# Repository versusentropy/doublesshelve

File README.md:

# doublesshelve

## WORK-IN-PROGRESSS - NOT TESTED YET

my stereo version of shelves done in KiCad.

CC-BY-SA 3.0 

Original by Emilie Gillet. Thank you for everything.
https://github.com/pichenettes/eurorack

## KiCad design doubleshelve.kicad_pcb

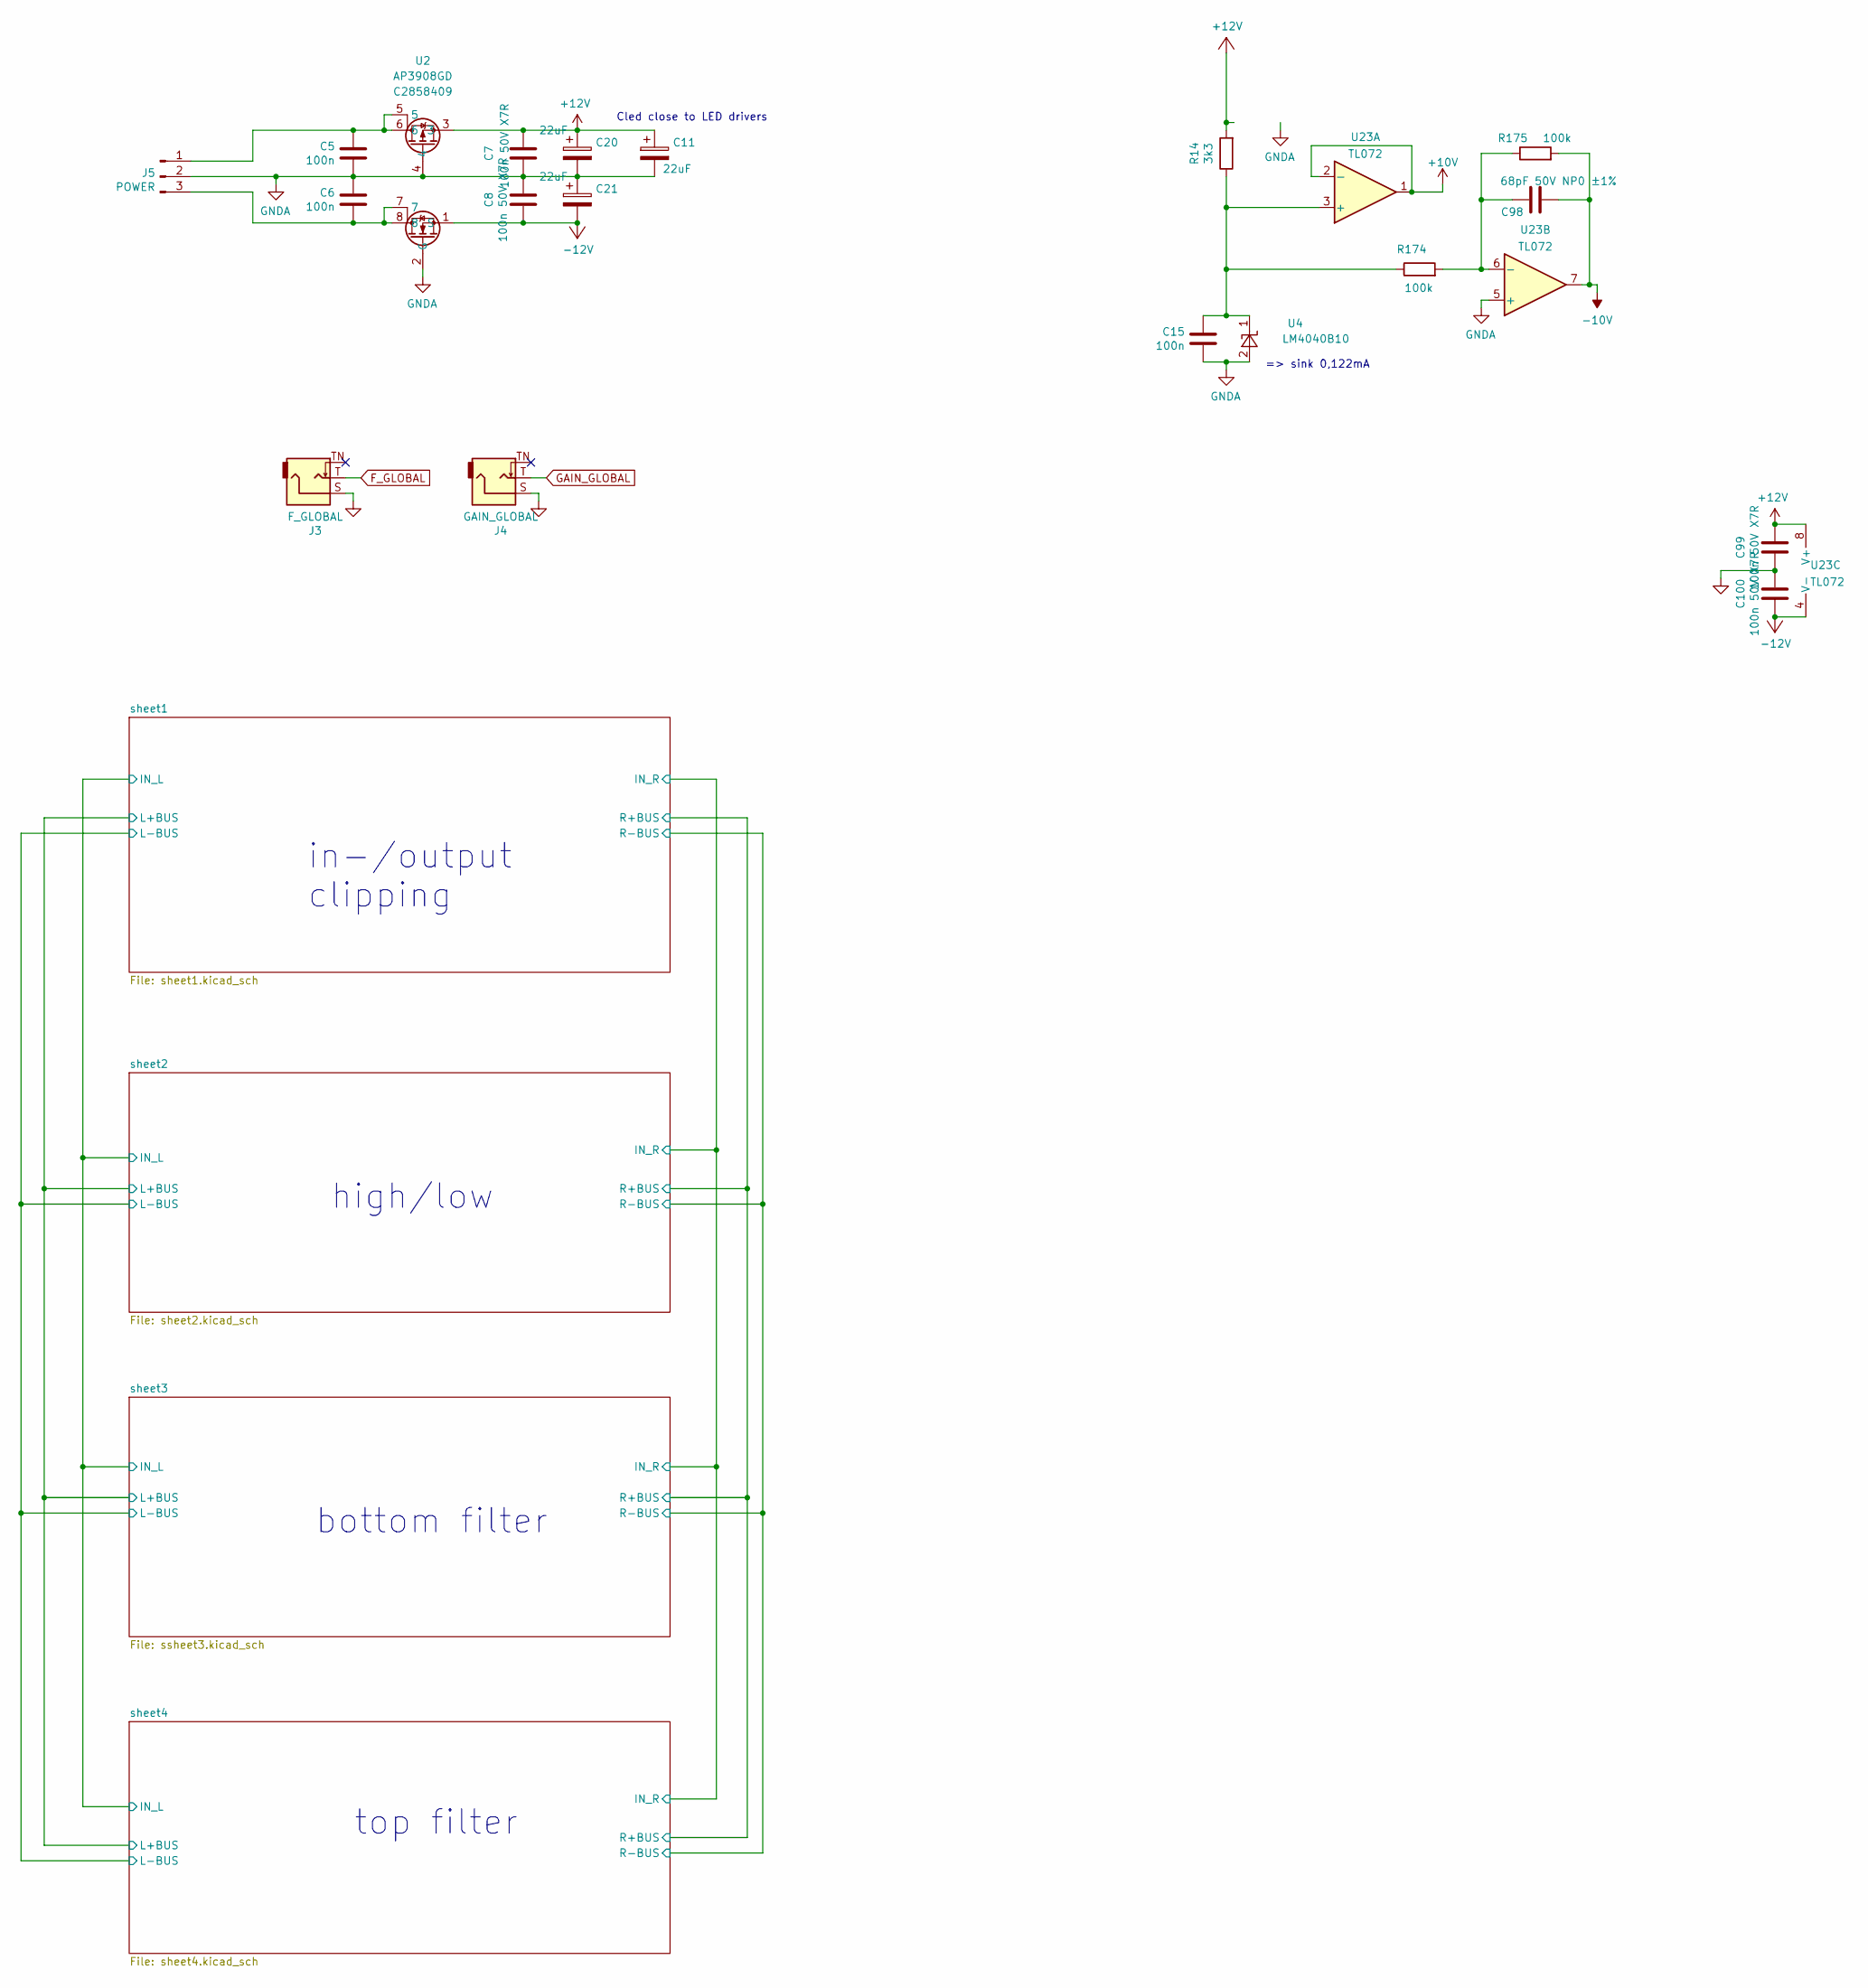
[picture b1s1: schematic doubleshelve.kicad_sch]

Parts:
C5, C6, C15: 100n; C_0402_1005Metric
C7, C8, C99, C100: 100n 50V X7R; C_0402_1005Metric; LCSC C307331
C11, C20, C21: 22uF; CP_Elec_5x5.3; LCSC C2163349
C98: 68pF 50V NP0 ±1%; C_0402_1005Metric; LCSC C5182453
J3: F_GLOBAL; Jack_3.5mm_QingPu_WQP-PJ398SM_Vertical_CircularHolesSMALL
J4: GAIN_GLOBAL; Jack_3.5mm_QingPu_WQP-PJ398SM_Vertical_CircularHolesSMALL
J5: POWER; eurorac_power-v2
R14: 3k3; R_0402_1005Metric
R174, R175: 100k; R_0402_1005Metric; LCSC C319963
U2: AP3908GD; LCSC C2858409
U4: LM4040B10; SOT-23
U23: TL072; SOIC-8_3.9x4.9mm_P1.27mm

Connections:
+10V: U23.1, U23.2 (-); also elsewhere on the board
+12V: C7.2, C11.1, C20.1, C99.2, R14.2, U2.3, U23.8 (V+); also elsewhere on the board
-10V: C98.1, R175.2, U23.7; also elsewhere on the board
-12V: C8.1, C21.2, C100.1, U2.1 (S), U23.4 (V-); also elsewhere on the board
F_GLOBAL: J3.T; also elsewhere on the board
GAIN_GLOBAL: J4.T; also elsewhere on the board
GNDA: C5.1, C6.2, C7.1, C8.2, C11.2, C15.1, C20.2, C21.1, C99.1, C100.2, J3.S, J4.S, J5.2, U2.2 (G), U2.4, U4.2 (A), U23.5 (+); also elsewhere on the board
unnamed: C5.2, J5.1, U2.5, U2.6
unnamed: C6.1, J5.3, U2.7, U2.8
unnamed: C15.2, R14.1, R174.1, U4.1 (K), U23.3 (+)
unnamed: C98.2, R174.2, R175.1, U23.6 (-)

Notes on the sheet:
Cled close to LED drivers
in-/output clipping
high/low
top filter
bottom filter
=> sink 0,122mA

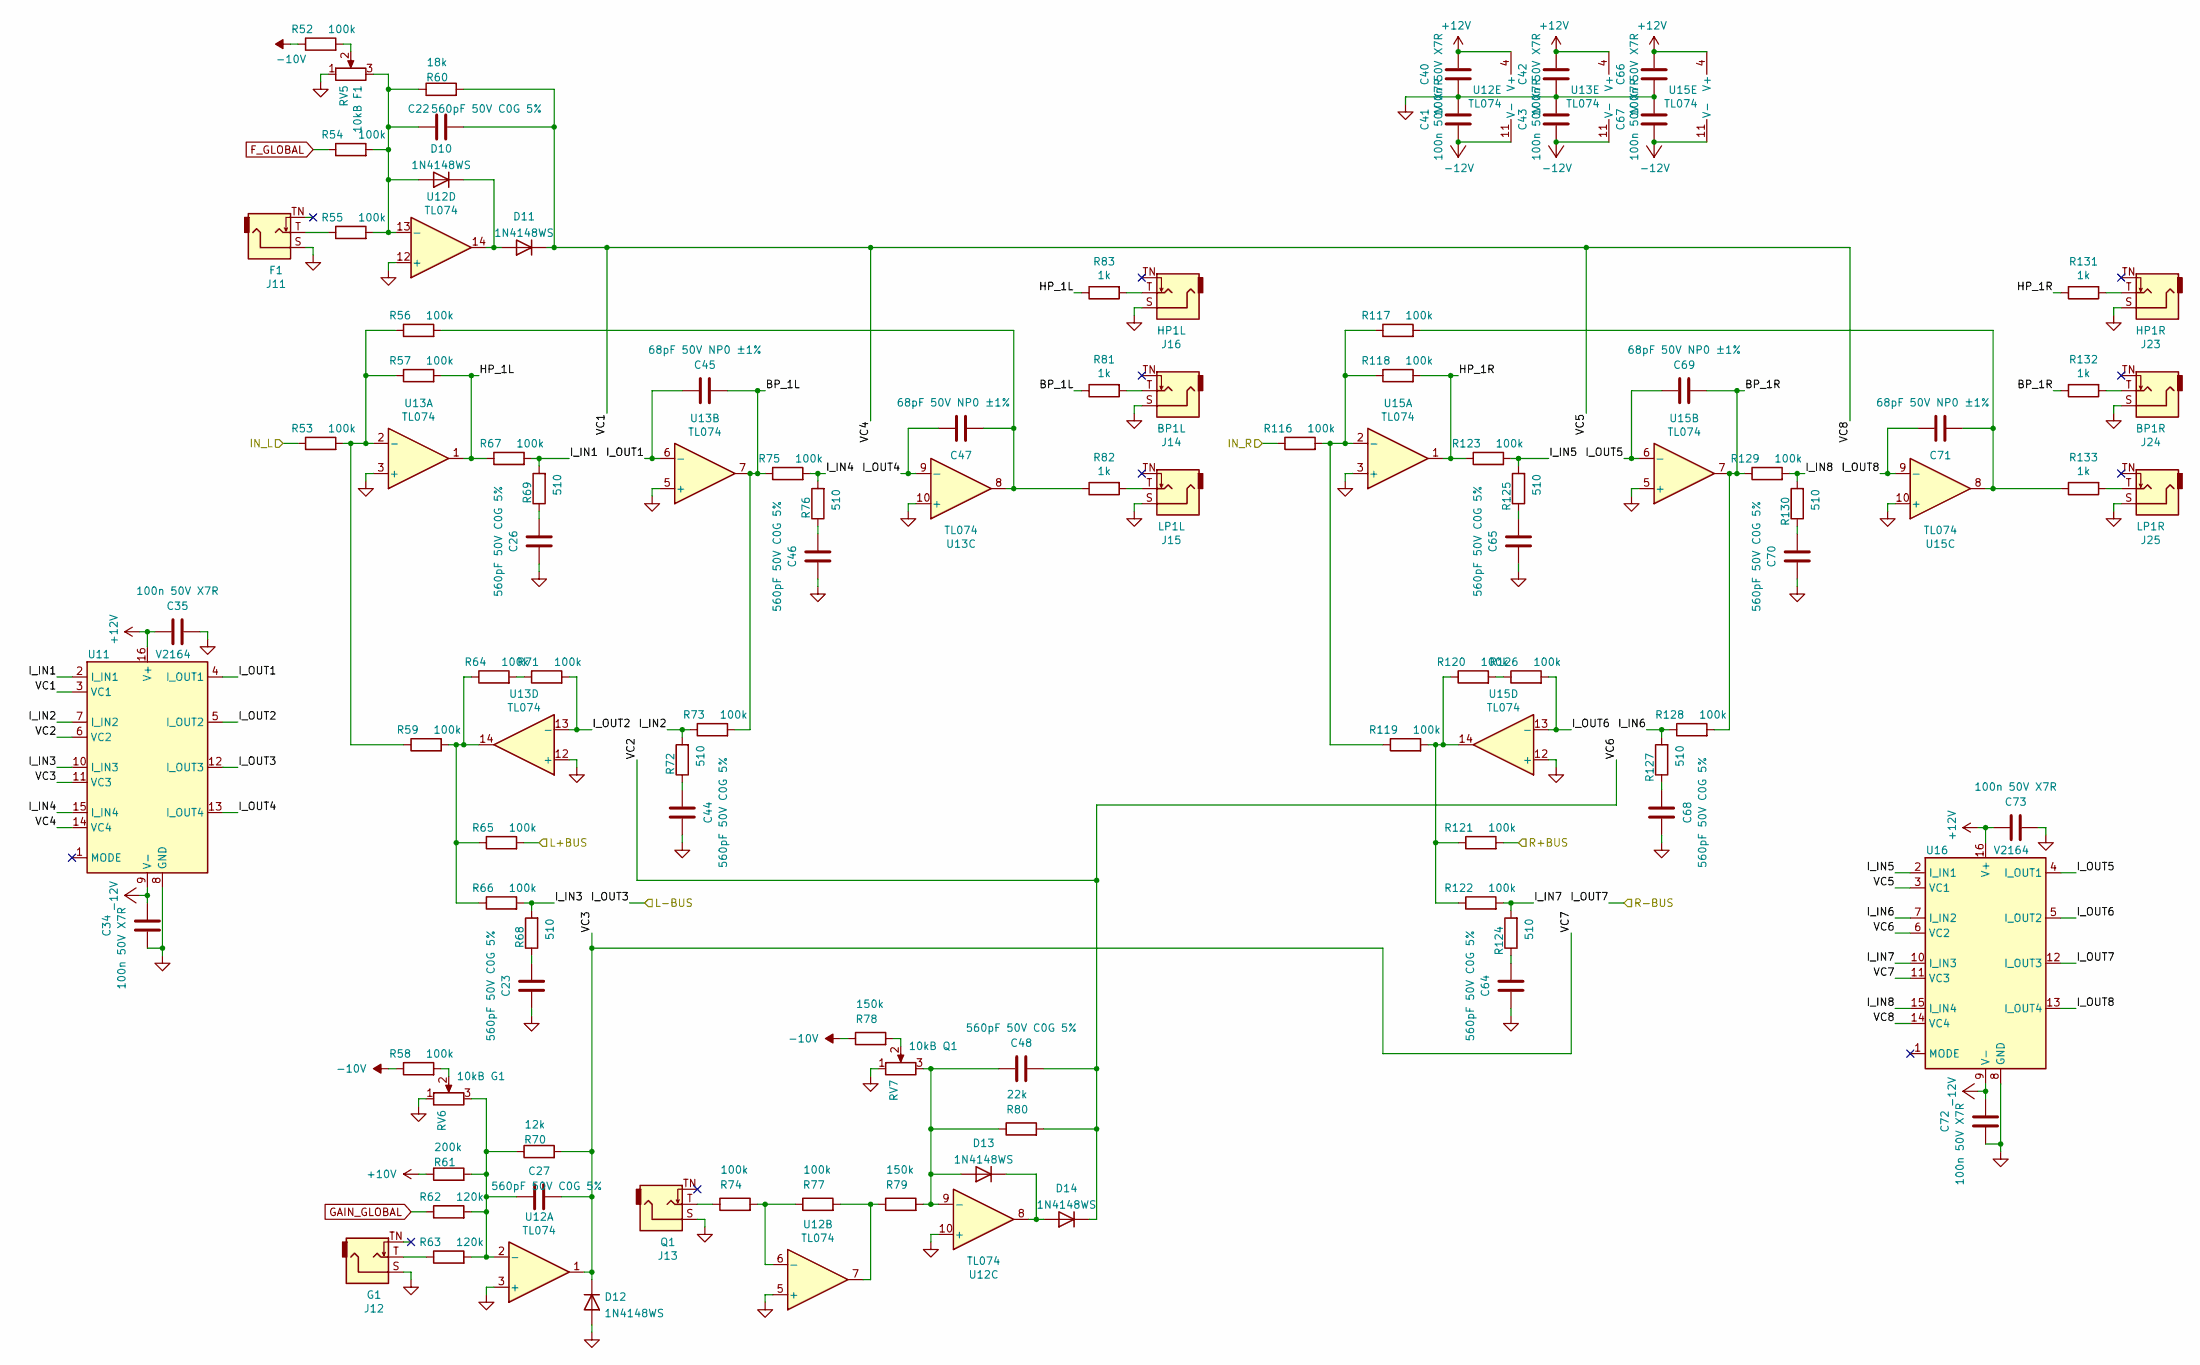
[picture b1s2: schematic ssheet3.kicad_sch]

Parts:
C22, C23, C26, C27, C44, C46, C48, C64, C65, C68, C70: 560pF 50V C0G 5%; C_0603_1608Metric; LCSC C97881
C34, C35, C40, C41, C42, C43, C66, C67, C72, C73: 100n 50V X7R; C_0402_1005Metric; LCSC C307331
C45, C47, C69, C71: 68pF 50V NP0 ±1%; C_0402_1005Metric; LCSC C5182453
D10, D11, D12, D13, D14: 1N4148WS; D_SOD-323; LCSC C2128
J11: F1; Jack_3.5mm_QingPu_WQP-PJ398SM_Vertical_CircularHolesSMALL
J12: G1; Jack_3.5mm_QingPu_WQP-PJ398SM_Vertical_CircularHolesSMALL
J13: Q1; Jack_3.5mm_QingPu_WQP-PJ398SM_Vertical_CircularHolesSMALL
J14: BP1L; Jack_3.5mm_QingPu_WQP-PJ398SM_Vertical_CircularHolesSMALL
J15: LP1L; Jack_3.5mm_QingPu_WQP-PJ398SM_Vertical_CircularHolesSMALL
J16: HP1L; Jack_3.5mm_QingPu_WQP-PJ398SM_Vertical_CircularHolesSMALL
J23: HP1R; Jack_3.5mm_QingPu_WQP-PJ398SM_Vertical_CircularHolesSMALL
J24: BP1R; Jack_3.5mm_QingPu_WQP-PJ398SM_Vertical_CircularHolesSMALL
J25: LP1R; Jack_3.5mm_QingPu_WQP-PJ398SM_Vertical_CircularHolesSMALL
R52, R53, R54, R55, R56, R57, R58, R59, R64, R65, R66, R67, R71, R73, R74, R75, R77, R116, R117, R118, R119, R120, R121, R122, R123, R126, R128, R129: 100k; R_0402_1005Metric; LCSC C319963
R60: 18k; R_0402_1005Metric
R61: 200k; R_0402_1005Metric
R62, R63: 120k; R_0402_1005Metric
R68, R69, R72, R76, R124, R125, R127, R130: 510; R_0402_1005Metric
R70: 12k; R_0402_1005Metric
R78, R79: 150k; R_0402_1005Metric
R80: 22k; R_0402_1005Metric
R81, R82, R83, R131, R132, R133: 1k; R_0603_1608Metric; LCSC C394536
RV5: 10kB F1; RD901F-ALPHA-POT
RV6: 10kB G1; RD901F-ALPHA-POT
RV7: 10kB Q1; RD901F-ALPHA-POT
U11, U16: V2164; SOIC-16_3.9x9.9mm_P1.27mm
U12, U13, U15: TL074; SOIC-14_3.9x8.7mm_P1.27mm; LCSC C96507

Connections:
+10V: R61.1; also elsewhere on the board
+12V: C35.2, C40.2, C42.2, C66.2, C73.2, U11.16 (V+), U12.4 (V+), U13.4 (V+), U15.4 (V+), U16.16 (V+); also elsewhere on the board
-10V: R52.1, R58.1, R78.1; also elsewhere on the board
-12V: C34.2, C41.1, C43.1, C67.1, C72.2, U11.9 (V-), U12.11 (V-), U13.11 (V-), U15.11 (V-), U16.9 (V-); also elsewhere on the board
/sheet1/IN_L: R53.1; also elsewhere on the board
/sheet1/IN_R: R116.1; also elsewhere on the board
/sheet1/L+BUS: R65.2; also elsewhere on the board
/sheet1/R+BUS: R121.2; also elsewhere on the board
/sheet3/BP_1L: C45.1, R73.2, R75.1, R81.1, U13.7
/sheet3/BP_1R: C69.1, R128.2, R129.1, R132.1, U15.7
/sheet3/HP_1L: R57.2, R67.1, R83.1, U13.1
/sheet3/HP_1R: R118.2, R123.1, R131.1, U15.1
/sheet3/I_IN1: R67.2, R69.2, U11.2 (I_IN1)
/sheet3/I_IN2: R72.2, R73.1, U11.7 (I_IN2)
/sheet3/I_IN3: R66.2, R68.2, U11.10 (I_IN3)
/sheet3/I_IN4: R75.2, R76.2, U11.15 (I_IN4)
/sheet3/I_IN5: R123.2, R125.2, U16.2 (I_IN1)
/sheet3/I_IN6: R127.2, R128.1, U16.7 (I_IN2)
/sheet3/I_IN7: R122.2, R124.2, U16.10 (I_IN3)
/sheet3/I_IN8: R129.2, R130.2, U16.15 (I_IN4)
/sheet3/I_OUT1: C45.2, U11.4 (I_OUT1), U13.6 (-)
/sheet3/I_OUT2: R71.2, U11.5 (I_OUT2), U13.13 (-)
/sheet3/I_OUT3: U11.12 (I_OUT3); also elsewhere on the board
/sheet3/I_OUT4: C47.2, U11.13 (I_OUT4), U13.9 (-)
/sheet3/I_OUT5: C69.2, U15.6 (-), U16.4 (I_OUT1)
/sheet3/I_OUT6: R126.2, U15.13 (-), U16.5 (I_OUT2)
/sheet3/I_OUT7: U16.12 (I_OUT3); also elsewhere on the board
/sheet3/I_OUT8: C71.2, U15.9 (-), U16.13 (I_OUT4)
/sheet3/VC1: C22.1, D11.1 (K), R60.2, U11.3 (VC1), U11.14 (VC4), U16.3 (VC1), U16.14 (VC4)
/sheet3/VC2: C48.1, D14.1 (K), R80.2, U11.6 (VC2), U16.6 (VC2)
/sheet3/VC3: C27.1, D12.1 (K), R70.2, U11.11 (VC3), U12.1, U16.11 (VC3)
F_GLOBAL: R54.1; also elsewhere on the board
GAIN_GLOBAL: R62.1; also elsewhere on the board
GNDA: C23.2, C26.2, C34.1, C35.1, C40.1, C41.2, C42.1, C43.2, C44.2, C46.2, C64.2, C65.2, C66.1, C67.2, C68.2, C70.2, C72.1, C73.1, D12.2 (A), J11.S, J12.S, J13.S, J14.S, J15.S, J16.S, J23.S, J24.S, J25.S, RV5.1, RV6.1, RV7.1, U11.8 (GND), U12.3 (+), U12.5 (+), U12.10 (+), U12.12 (+), U13.3 (+), U13.5 (+), U13.10 (+), U13.12 (+), U15.3 (+), U15.5 (+), U15.10 (+), U15.12 (+), U16.8 (GND); also elsewhere on the board
unnamed: C23.1, R68.1
unnamed: C26.1, R69.1
unnamed: C44.1, R72.1
unnamed: C46.1, R76.1
unnamed: C47.1, R56.2, R82.1, U13.8
unnamed: C64.1, R124.1
unnamed: C65.1, R125.1
unnamed: C68.1, R127.1
unnamed: C70.1, R130.1
unnamed: C71.1, R117.2, R133.1, U15.8
unnamed: C22.2, D10.2 (A), R54.2, R55.2, R60.1, RV5.3, U12.13 (-)
unnamed: D10.1 (K), D11.2 (A), U12.14
unnamed: C48.2, D13.2 (A), R79.2, R80.1, RV7.3, U12.9 (-)
unnamed: D13.1 (K), D14.2 (A), U12.8
unnamed: J11.T, R55.1
unnamed: J12.T, R63.1
unnamed: J13.T, R74.1
unnamed: J14.T, R81.2
unnamed: J15.T, R82.2
unnamed: J16.T, R83.2
unnamed: J23.T, R131.2
unnamed: J24.T, R132.2
unnamed: J25.T, R133.2
unnamed: R52.2, RV5.2
unnamed: R58.2, RV6.2
unnamed: R59.2, R64.1, R65.1, R66.1, U13.14
unnamed: R64.2, R71.1
unnamed: R77.2, R79.1, U12.7
unnamed: R78.2, RV7.2
unnamed: R119.2, R120.1, R121.1, R122.1, U15.14
unnamed: R120.2, R126.1
unnamed: C27.2, R61.2, R62.2, R63.2, R70.1, RV6.3, U12.2 (-)
unnamed: R74.2, R77.1, U12.6 (-)
unnamed: R53.2, R56.1, R57.1, R59.1, U13.2 (-)
unnamed: R116.2, R117.1, R118.1, R119.1, U15.2 (-)

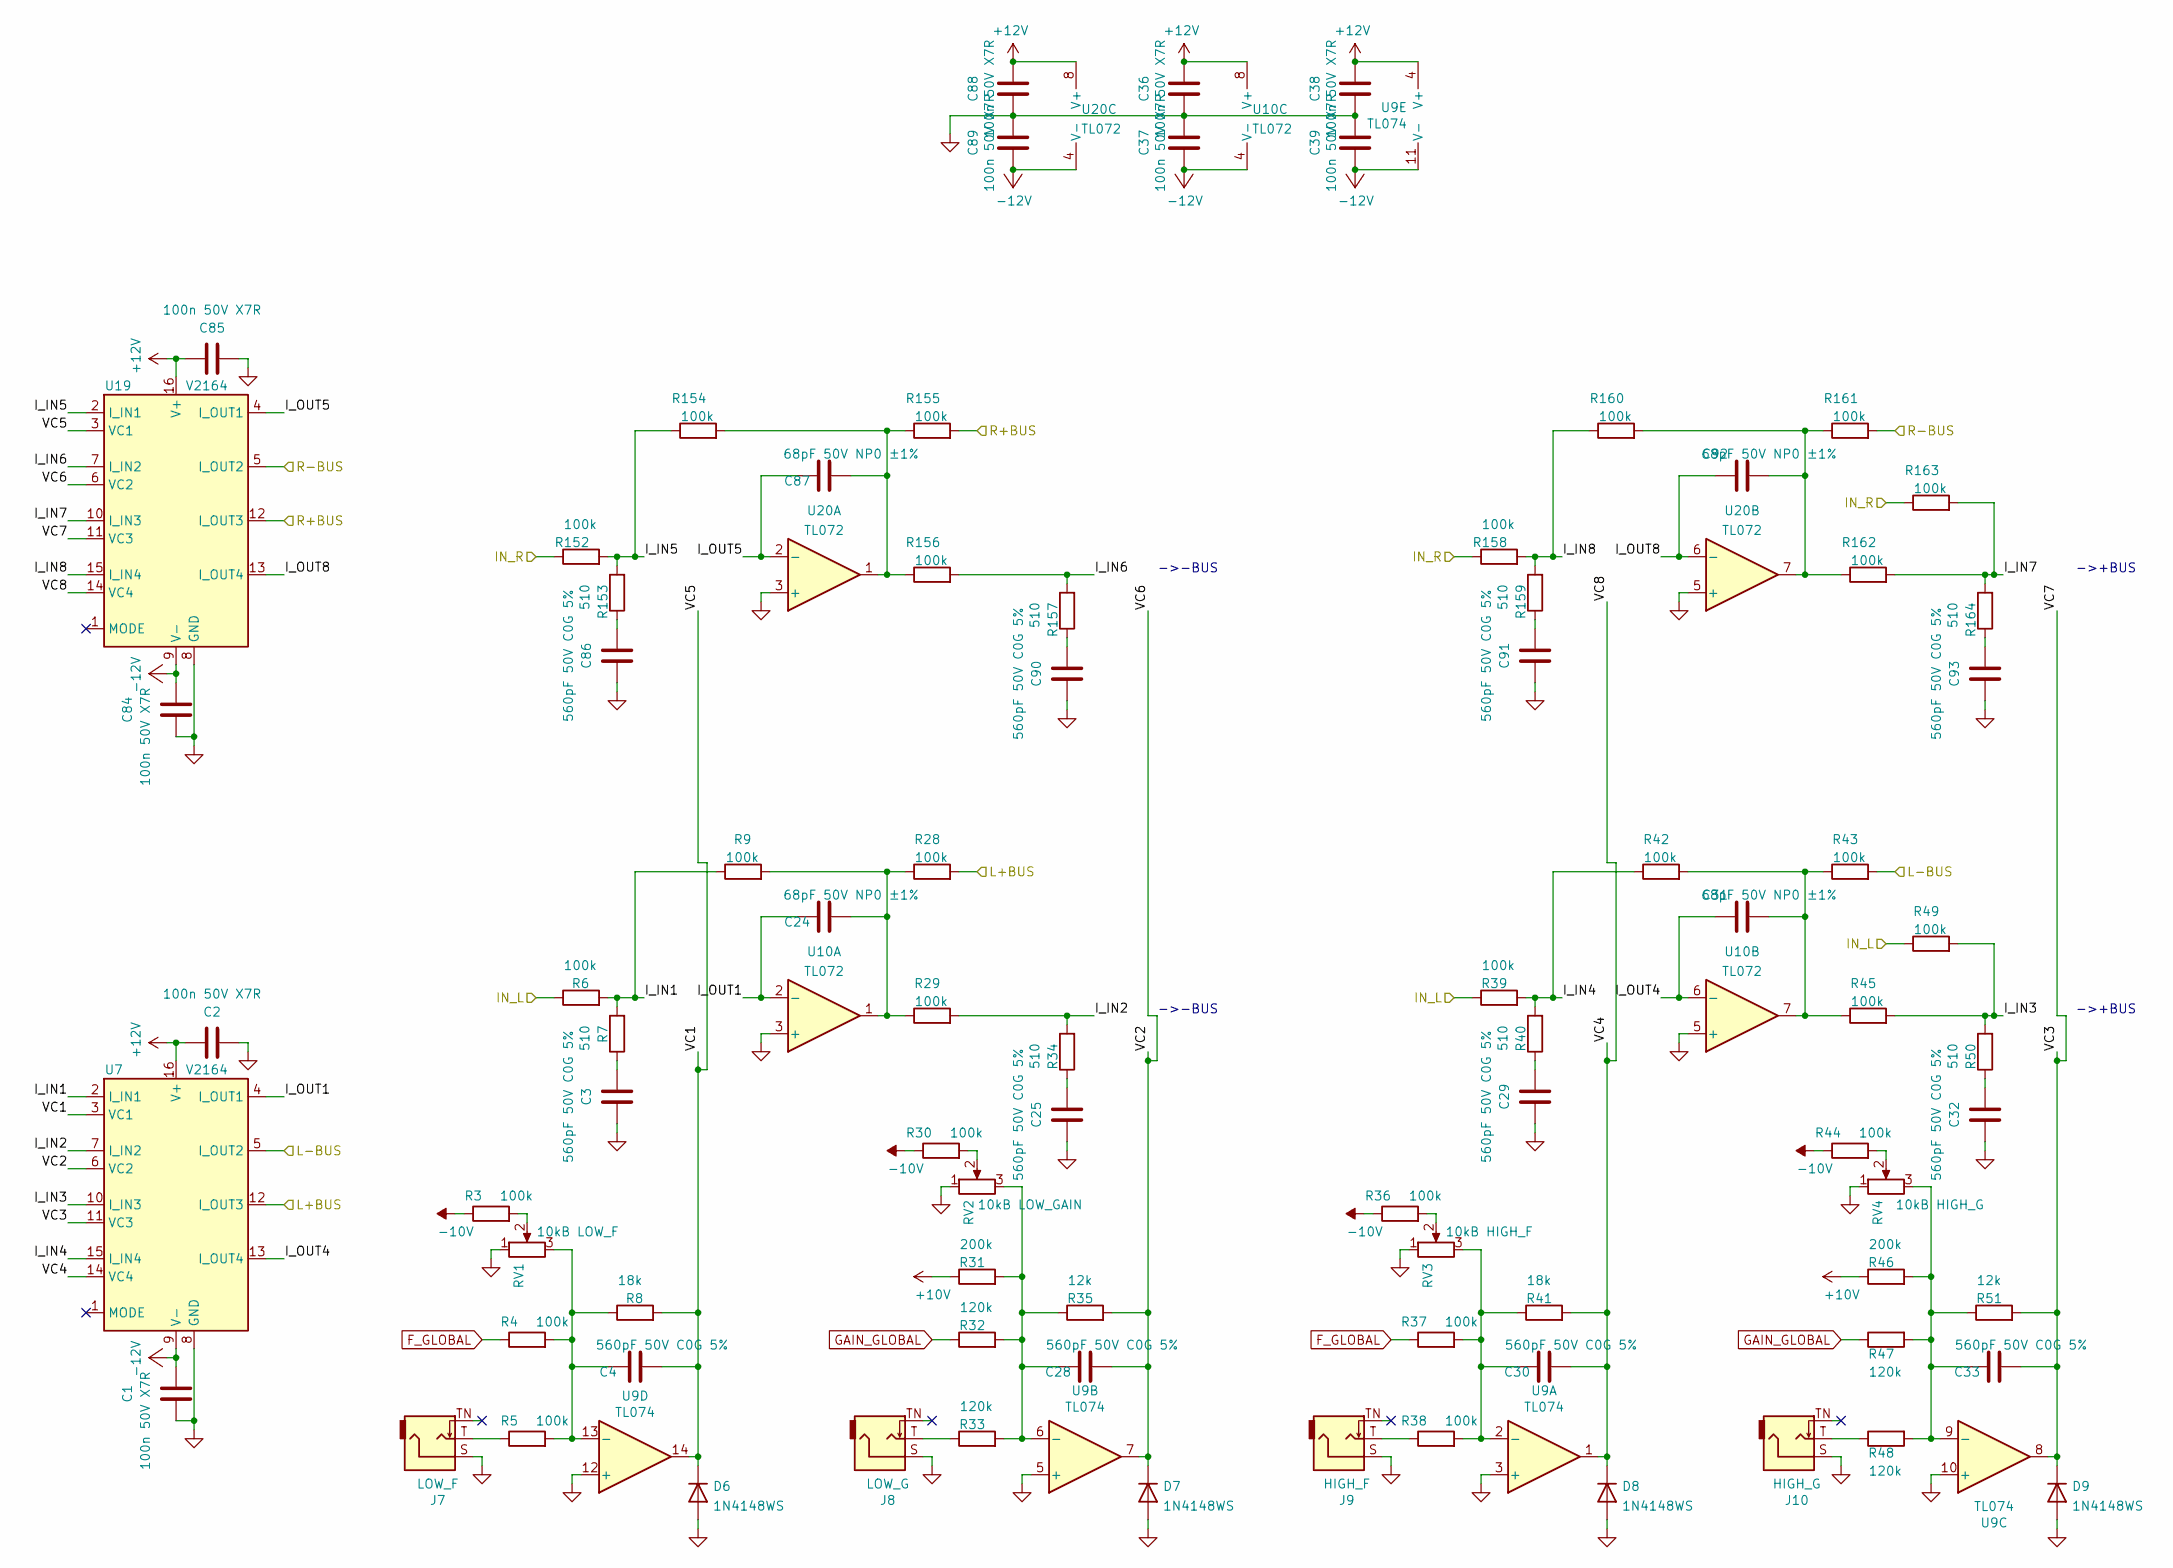
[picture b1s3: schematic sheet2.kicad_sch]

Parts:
C1, C2, C36, C37, C38, C39, C84, C85, C88, C89: 100n 50V X7R; C_0402_1005Metric; LCSC C307331
C3, C4, C25, C28, C29, C30, C32, C33, C86, C90, C91, C93: 560pF 50V C0G 5%; C_0603_1608Metric; LCSC C97881
C24, C31, C87, C92: 68pF 50V NP0 ±1%; C_0402_1005Metric; LCSC C5182453
D6, D7, D8, D9: 1N4148WS; D_SOD-323; LCSC C2128
J7: LOW_F; Jack_3.5mm_QingPu_WQP-PJ398SM_Vertical_CircularHolesSMALL
J8: LOW_G; Jack_3.5mm_QingPu_WQP-PJ398SM_Vertical_CircularHolesSMALL
J9: HIGH_F; Jack_3.5mm_QingPu_WQP-PJ398SM_Vertical_CircularHolesSMALL
J10: HIGH_G; Jack_3.5mm_QingPu_WQP-PJ398SM_Vertical_CircularHolesSMALL
R3, R4, R5, R6, R9, R28, R29, R30, R36, R37, R38, R39, R42, R43, R44, R45, R49, R152, R154, R155, R156, R158, R160, R161, R162, R163: 100k; R_0402_1005Metric; LCSC C319963
R7, R34, R40, R50, R153, R157, R159, R164: 510; R_0402_1005Metric
R8, R41: 18k; R_0402_1005Metric
R31, R46: 200k; R_0402_1005Metric
R32, R33, R47, R48: 120k; R_0402_1005Metric
R35, R51: 12k; R_0402_1005Metric
RV1: 10kB LOW_F; RD901F-ALPHA-POT
RV2: 10kB LOW_GAIN; RD901F-ALPHA-POT
RV3: 10kB HIGH_F; RD901F-ALPHA-POT
RV4: 10kB HIGH_G; RD901F-ALPHA-POT
U7, U19: V2164; SOIC-16_3.9x9.9mm_P1.27mm
U9: TL074; SOIC-14_3.9x8.7mm_P1.27mm; LCSC C96507
U10, U20: TL072; SOIC-8_3.9x4.9mm_P1.27mm

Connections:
+10V: R31.1, R46.1; also elsewhere on the board
+12V: C2.2, C36.2, C38.2, C85.2, C88.2, U7.16 (V+), U9.4 (V+), U10.8 (V+), U19.16 (V+), U20.8 (V+); also elsewhere on the board
-10V: R3.1, R30.1, R36.1, R44.1; also elsewhere on the board
-12V: C1.2, C37.1, C39.1, C84.2, C89.1, U7.9 (V-), U9.11 (V-), U10.4 (V-), U19.9 (V-), U20.4 (V-); also elsewhere on the board
/sheet1/IN_L: R6.1, R39.1, R49.1; also elsewhere on the board
/sheet1/IN_R: R152.1, R158.1, R163.1; also elsewhere on the board
/sheet1/L+BUS: R28.2, U7.12 (I_OUT3); also elsewhere on the board
/sheet1/R+BUS: R155.2, U19.12 (I_OUT3); also elsewhere on the board
/sheet2/I_IN1: R6.2, R7.2, R9.1, U7.2 (I_IN1)
/sheet2/I_IN2: R29.2, R34.2, U7.7 (I_IN2)
/sheet2/I_IN3: R45.2, R49.2, R50.2, U7.10 (I_IN3)
/sheet2/I_IN4: R39.2, R40.2, R42.1, U7.15 (I_IN4)
/sheet2/I_IN5: R152.2, R153.2, R154.1, U19.2 (I_IN1)
/sheet2/I_IN6: R156.2, R157.2, U19.7 (I_IN2)
/sheet2/I_IN7: R162.2, R163.2, R164.2, U19.10 (I_IN3)
/sheet2/I_IN8: R158.2, R159.2, R160.1, U19.15 (I_IN4)
/sheet2/I_OUT1: C24.2, U7.4 (I_OUT1), U10.2 (-)
/sheet2/I_OUT4: C31.2, U7.13 (I_OUT4), U10.6 (-)
/sheet2/I_OUT5: C87.2, U19.4 (I_OUT1), U20.2 (-)
/sheet2/I_OUT8: C92.2, U19.13 (I_OUT4), U20.6 (-)
/sheet2/VC1: C4.1, D6.1 (K), R8.2, U7.3 (VC1), U9.14, U19.3 (VC1)
/sheet2/VC2: C28.1, D7.1 (K), R35.2, U7.6 (VC2), U9.7, U19.6 (VC2)
/sheet2/VC3: C33.1, D9.1 (K), R51.2, U7.11 (VC3), U9.8, U19.11 (VC3)
/sheet2/VC4: C30.1, D8.1 (K), R41.2, U7.14 (VC4), U9.1, U19.14 (VC4)
/sheet3/I_OUT3: R43.2, U7.5 (I_OUT2); also elsewhere on the board
/sheet3/I_OUT7: R161.2, U19.5 (I_OUT2); also elsewhere on the board
F_GLOBAL: R4.1, R37.1; also elsewhere on the board
GAIN_GLOBAL: R32.1, R47.1; also elsewhere on the board
GNDA: C1.1, C2.1, C3.2, C25.2, C29.2, C32.2, C36.1, C37.2, C38.1, C39.2, C84.1, C85.1, C86.2, C88.1, C89.2, C90.2, C91.2, C93.2, D6.2 (A), D7.2 (A), D8.2 (A), D9.2 (A), J7.S, J8.S, J9.S, J10.S, RV1.1, RV2.1, RV3.1, RV4.1, U7.8 (GND), U9.3 (+), U9.5 (+), U9.10 (+), U9.12 (+), U10.3 (+), U10.5 (+), U19.8 (GND), U20.3 (+), U20.5 (+); also elsewhere on the board
unnamed: C3.1, R7.1
unnamed: C24.1, R9.2, R28.1, R29.1, U10.1
unnamed: C25.1, R34.1
unnamed: C29.1, R40.1
unnamed: C31.1, R42.2, R43.1, R45.1, U10.7
unnamed: C32.1, R50.1
unnamed: C86.1, R153.1
unnamed: C87.1, R154.2, R155.1, R156.1, U20.1
unnamed: C90.1, R157.1
unnamed: C91.1, R159.1
unnamed: C92.1, R160.2, R161.1, R162.1, U20.7
unnamed: C93.1, R164.1
unnamed: J7.T, R5.1
unnamed: J8.T, R33.1
unnamed: J9.T, R38.1
unnamed: J10.T, R48.1
unnamed: R3.2, RV1.2
unnamed: R30.2, RV2.2
unnamed: R36.2, RV3.2
unnamed: R44.2, RV4.2
unnamed: C30.2, R37.2, R38.2, R41.1, RV3.3, U9.2 (-)
unnamed: C28.2, R31.2, R32.2, R33.2, R35.1, RV2.3, U9.6 (-)
unnamed: C33.2, R46.2, R47.2, R48.2, R51.1, RV4.3, U9.9 (-)
unnamed: C4.2, R4.2, R5.2, R8.1, RV1.3, U9.13 (-)

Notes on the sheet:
->-BUS
->+BUS
